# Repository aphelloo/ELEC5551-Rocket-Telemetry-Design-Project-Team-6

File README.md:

# ELEC5551-Rocket-Telemetry-Design-Project-Team-6
The purpose of this final design report is to present a TTS design for the UWAAL sub-orbital launch project. The design primarily aims to track the rocket’s sub-orbital launch to 4 km altitude, monitor its descent, identify the landing location for recovery efforts whilst also collect data throughout the entire mission. This is achieved through the development of two modules: one fitting within the designated section of the CubeSat onboard the rocket (i.e. the payload module) that collects & transmits data, and a base station on the ground responsible for collecting information from the payload module and displaying location of the payload module on a user interface akin to Google Maps functionality. The final design will be composed of a hardware and software solution that will address the inclusions stated in this section.

## Authors
* Shraddha Domdala 
* Sharla Greyvenstein 
* Kate Miller 
* Ankona Pahari
* Anusree Rejukumar
* Thomas Robertson

## Repository Structure
* 3D CAD Design: For Base Station Box and Battery Holder (payload module)
* Code: Includes pseudocode and code-flow diagrams
* Construction and Risks: Documentation on construction procedures and risk assessments associated with the project.
* Libraries: Libraries required for KiCAD to open schematics and PCB Layout
* PCB Layout: PCB Layout for base station and payload module
* Schematics: Schematics for base station and payload module
* Simulations: Simulations to test various aspects of the project

## Required Applications
* KiCAD V6 or Later
* MATLAB 2024a

## Library Installation Guide
Under Libraries
Using the *.kicad_sym file:

* Extract the content of the downloaded *.zip file.
* In KiCad, go to Preferences.
* Click on Manage Symbol Libraries.
* On the Global Libraries tab, click on Browse Libraries (the small folder icon)
* Select the .kicad_sym file, then click Open.
* The library will appear, click OK.
* Click on Symbol Editor.
* Type on the filter search field, and navigate to the symbol you imported.
* Double-click over it to open the file.

Using the *.kicad_mod file:

* Extract the content of the downloaded *.zip file.
* In KiCad, go to Preferences.
* Click on Manage Footprint Libraries.
* On the Global Libraries tab, click on Browse Libraries (the small folder icon)
* Navigate to the Folder where the .kicad_mod file is located. Then click Select Folder. (Note: You will not normally see the .kicad_mod file on this step because
  you need to select the folder where it is located.)
* The library will appear, click OK.
* Click on Footprint Editor.
* Type on the filter search field, and navigate to the footprint you imported.
* Double-click over it to open the file.

## Simulation File Installation Guide 
Files are under simulations > spice simulations
* Extract the content of the downloaded *.zip file.
* Go to the voltage regulator and right click on properties
* Then click on Simulation Model
* Click folder near the file tab
* Go to location of LM1117_N_ADJ_TRANS.LIB or TPS7A0530P_TRANS.lib depending on the file (see name of component to see which is right) - do not change anything else in that tab
* Ensure pin assignments for symbol and model pin match each other in the Simulation Model
* Click Ok in Simulation Model
* Click Ok in Properties Tab

## Acknowledgements
Would like to acknowledge the stakeholders of this project for their assistance

## Licence
This project is licensed under the CERN-OHL-P-2.0 license

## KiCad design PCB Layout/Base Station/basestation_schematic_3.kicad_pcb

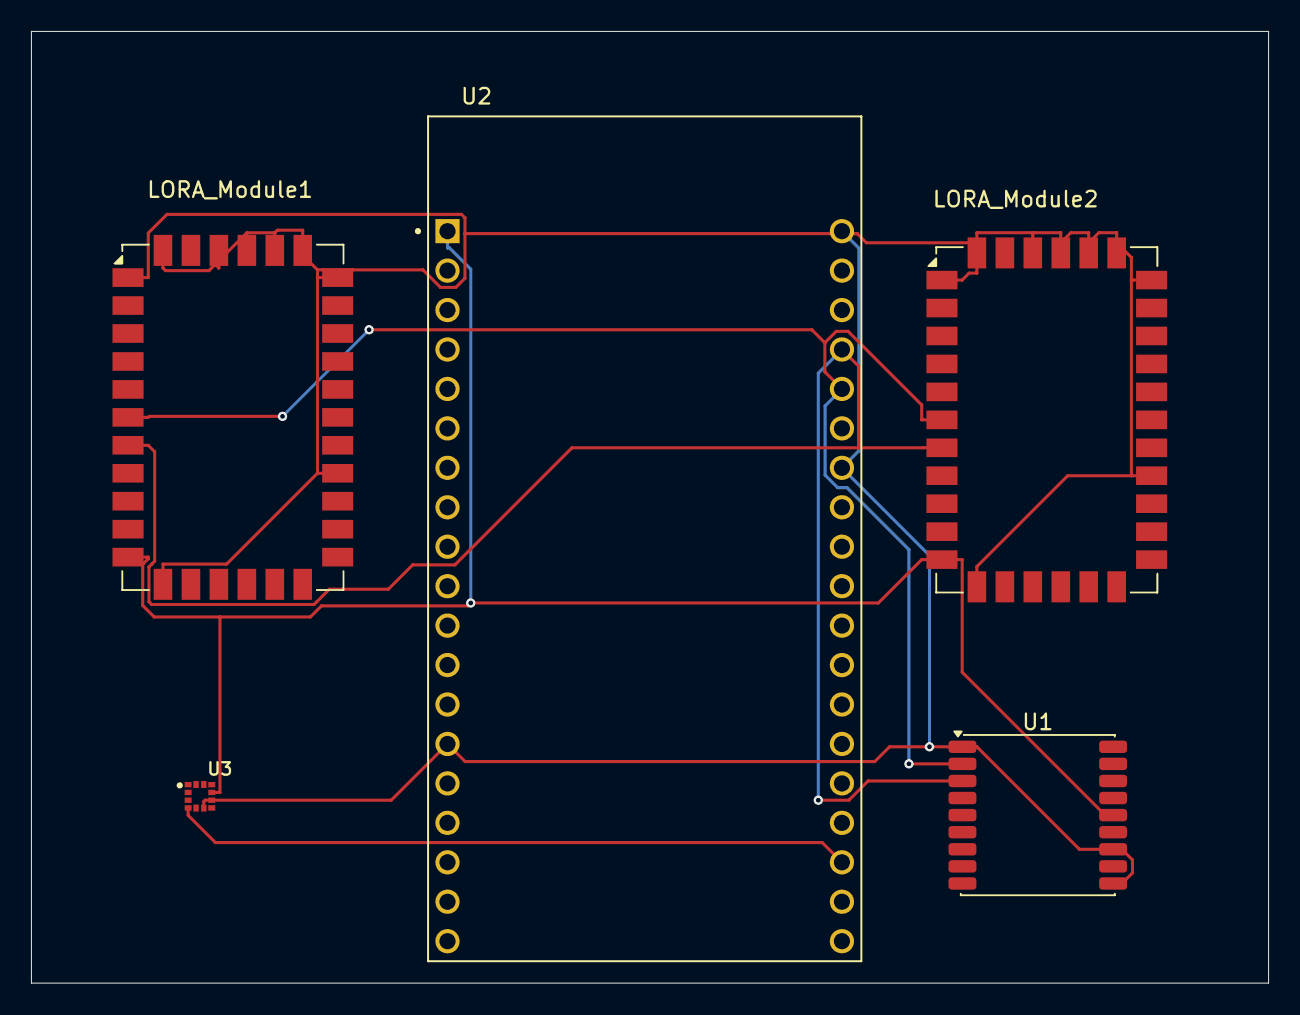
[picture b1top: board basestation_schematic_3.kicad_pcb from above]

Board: 2 copper layers, 79.7 x 61.3 mm, 5 parts (0 on the bottom side), 5 nets.

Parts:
LORA_Module1, LORA_Module2: RAK811-LF-CN470; RAK811
U1: L70-R; Quectel_L70-R
U2: ESP32-DEVKITC-32D; MODULE_ESP32-DEVKITC-32D
U3: LSM303AGRTR; LGA12R50P_200X200X100

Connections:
GNDREF: LORA_Module1.1 (GND), LORA_Module1.12 (GND), LORA_Module1.21 (GND), LORA_Module1.28 (GND), LORA_Module1.29 (GND), LORA_Module1.30 (GND), LORA_Module1.31 (GND), LORA_Module1.32 (GND), LORA_Module1.34 (GND), LORA_Module2.1 (GND), LORA_Module2.12 (GND), LORA_Module2.21 (GND), LORA_Module2.28 (GND), LORA_Module2.29 (GND), LORA_Module2.30 (GND), LORA_Module2.31 (GND), LORA_Module2.32 (GND), LORA_Module2.34 (GND), U1.1 (GND), U1.10 (GND), U1.12 (GND), U2.J2-14 (GND1), U2.J3-1 (GND3), U2.J3-7 (GND2), U3.6 (GND), U3.8 (GND)
unnamed: LORA_Module1.6 (PA9/USART1_TX), LORA_Module2.6 (PA9/USART1_TX), U1.2 (TXD1), U2.J3-5 (RXD0)
unnamed: LORA_Module1.7 (PA10/USART1_RX), LORA_Module2.7 (PA10/USART1_RX), U1.3 (RXD1), U2.J3-4 (TXD0)
unnamed: LORA_Module1.11 (VCC), LORA_Module2.11 (VCC), U1.14 (VCC_RF), U2.J2-1 (3V3), U3.9 (VDD)
unnamed: U2.J3-17 (SD1), U3.4 (SDA/SDI/SDO)

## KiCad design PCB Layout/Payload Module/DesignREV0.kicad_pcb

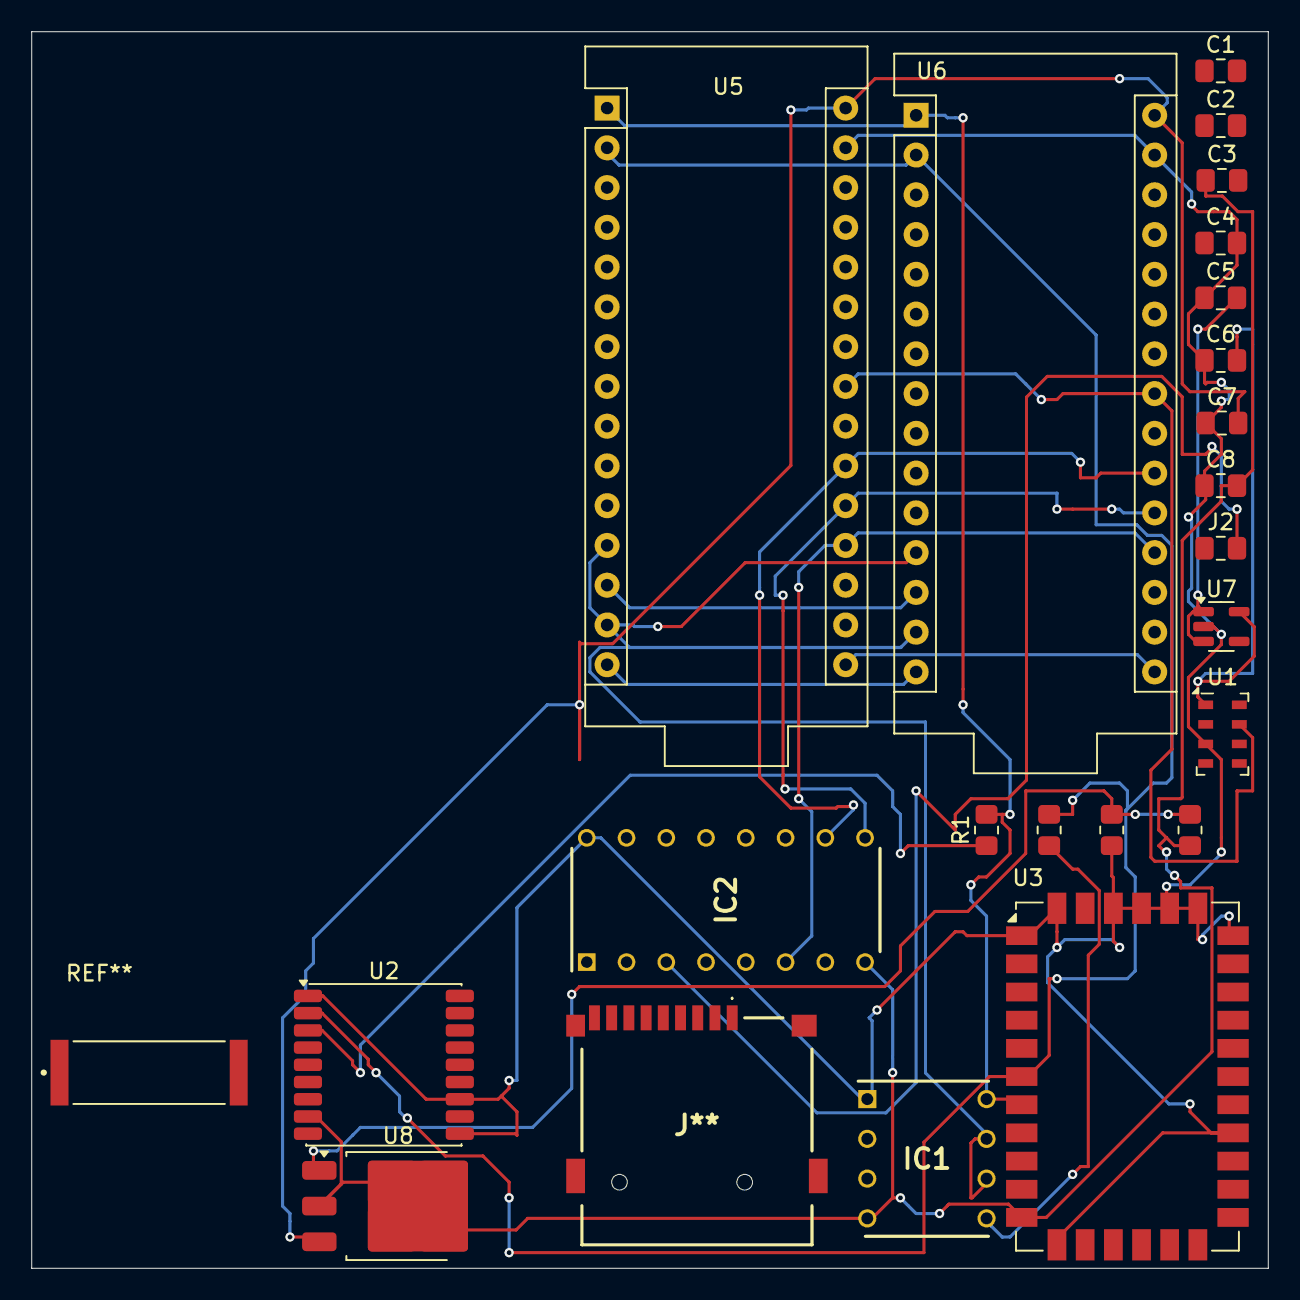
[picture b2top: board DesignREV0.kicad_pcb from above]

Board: 2 copper layers, 79.0 x 79.0 mm, 23 parts (0 on the bottom side), 19 nets.

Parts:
C1, C2, C3, C4: 10u; C_0805_2012Metric_Pad1.18x1.45mm_HandSolder
C5, C6: 0.1U; C_0805_2012Metric_Pad1.18x1.45mm_HandSolder
C7: 10U; C_0805_2012Metric_Pad1.18x1.45mm_HandSolder
C8: 100U; C_0805_2012Metric_Pad1.18x1.45mm_HandSolder
IC1: MAX485EPA+; DIP762W56P254L938H457Q8N
IC2: CD4052BE; DIP794W53P254L1930H508Q16N
J2: DE9_Plug; C_0805_2012Metric_Pad1.18x1.45mm_HandSolder
J**: MICROSDCARD
R1, R2: 4.7k; R_0805_2012Metric_Pad1.20x1.40mm_HandSolder
R3: 1k; R_0805_2012Metric_Pad1.20x1.40mm_HandSolder
R4: 3k; R_0805_2012Metric_Pad1.20x1.40mm_HandSolder
U1: MS5607-02BA; LGA-8_3x5mm_P1.25mm
U2: L70-R; Quectel_L70-R
U3: RAK811-LF-CN470; RAK811
U5, U6: Arduino_Nano
U7: TPS7A0530PDBV; SOT-23-5
U8: LM1117DT-ADJ; TO-252-3_TabPin2

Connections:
GND: C4.2, C5.1, C6.1, C7.1, C8.1, IC1.1 (RO), IC2.16 (VDD), R4.1, U1.3 (GND), U2.1 (GND), U2.10 (GND), U2.12 (GND), U3.1 (GND), U3.12 (GND), U3.21 (GND), U3.28 (GND), U3.29 (GND), U3.30 (GND), U3.31 (GND), U3.32 (GND), U3.34 (GND), U5.29 (GND), U6.29 (GND), U7.2 (GND)
unnamed: C5.2, U7.1 (IN), U7.3 (EN)
unnamed: C7.2, U5.30 (VIN), U6.30 (VIN), U8.3 (VI)
unnamed: IC1.6 (A), IC1.7 (B), U5.12 (~D9), U5.14 (~D11), U6.12 (~D9), U6.14 (~D11)
unnamed: C3.1, C8.2, IC1.4 (DI), IC2.8 (VSS), R3.1, U2.8 (VCC), U3.11 (VCC), U8.2 (VO)
unnamed: IC1.5 (GND), R2.1
unnamed: IC1.8 (VCC), R1.2, U3.7 (PA10/USART1_RX), U5.1 (D1/TX), U6.1 (D1/TX)
unnamed: IC2.10 (A), U5.21 (A2/D16), U6.21 (A2/D16)
unnamed: IC2.9 (B), U5.20 (A1/D15), U6.20 (A1/D15)
unnamed: IC2.3 (COMMON_“Y”_OUT/IN), J2.2
unnamed: IC2.6 (INH), U5.19 (A0/D14), U6.19 (A0/D14)
unnamed: U5.16 (D13), U6.16 (D13)
unnamed: U5.15 (D12), U6.15 (D12)
unnamed: U5.13 (~D10), U6.13 (~D10)
unnamed: U1.7 (SDI/SDA), U5.23 (A4/D18), U6.23 (A4/D18)
unnamed: C6.2, U1.1 (VDD), U7.5 (OUT)
unnamed: R1.1, U2.3 (RXD1)
unnamed: R2.2, U2.2 (TXD1), U3.6 (PA9/USART1_TX), U5.2 (D0/RX), U6.2 (D0/RX)
unnamed: R3.2, R4.2, U8.1 (ADJ)

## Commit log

2024-05-18 Create LICENSE
    Open source / open hardware license
2024-05-18 Create README for Simulations
2024-05-18 Create Sims
2024-05-18 Create RF Link Simulations
2024-05-18 Create README for Schematics
2024-05-18 Create README for PCB Layout
2024-05-18 Create README for RF Simulations
2024-05-18 Create README for Thermal Management
2024-05-18 Create README for Battery Lifetime
2024-05-18 Create README for Code Flow
2024-05-18 Create README for Pseudocode
2024-05-26 Create Risks
2024-05-26 Create 3D CAD Design Folder
2024-05-26 Create folder for Risks and Constructions
2024-05-26 Create Requirements
2024-05-26 Battery Design Documentation
    The battery design documentation for telemetry or tracking of a rocket payload includes numerous critical sections to guarantee that all components of the project are fully covered. The introduction 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
2024-05-26 Update Battery Design Documentation
2024-05-27 Add files via upload
    3D Print of Base Station Box and Battery Holder
2024-05-27 Code Flow Addition
2024-05-27 Create User Interface Pseudocode
2024-05-27 Create Power Management Code
2024-05-27 Create Webpage Set Up
2024-05-27 Create Compass Display and Triangulation
2024-05-27 Create GPS Initialisation
2024-05-27 Create WiFi Setup
2024-05-27 Create base station
2024-05-27 Create libraries
2024-05-27 Update Power Management
